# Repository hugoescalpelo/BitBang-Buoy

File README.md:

# BitBang-Buoy

A project from Iván Abreu's Studio to simulate wave movement through a pendant system

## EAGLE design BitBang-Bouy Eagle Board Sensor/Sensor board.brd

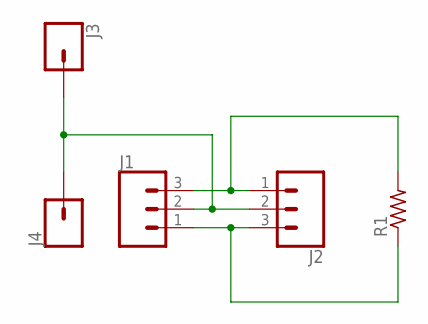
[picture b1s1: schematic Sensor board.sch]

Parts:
J1, J2: CONN_03LONGPADS; 1X03_LONGPADS
J3, J4: CONN_01SMTSO-256-ET-0.165DIA; SMTSO-256-ET-0.165DIA
R1: R-US_0204/7; 0204/7

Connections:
unnamed: J1.3, J2.1, R1.2
unnamed: J1.2, J2.2, J3.P$1, J4.P$1
unnamed: J1.1, J2.3, R1.1

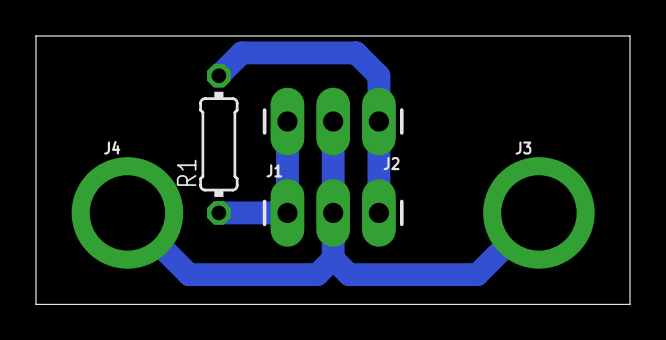
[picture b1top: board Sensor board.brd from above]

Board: 2 copper layers, 33.0 x 14.9 mm, 5 parts (0 on the bottom side), 3 nets.

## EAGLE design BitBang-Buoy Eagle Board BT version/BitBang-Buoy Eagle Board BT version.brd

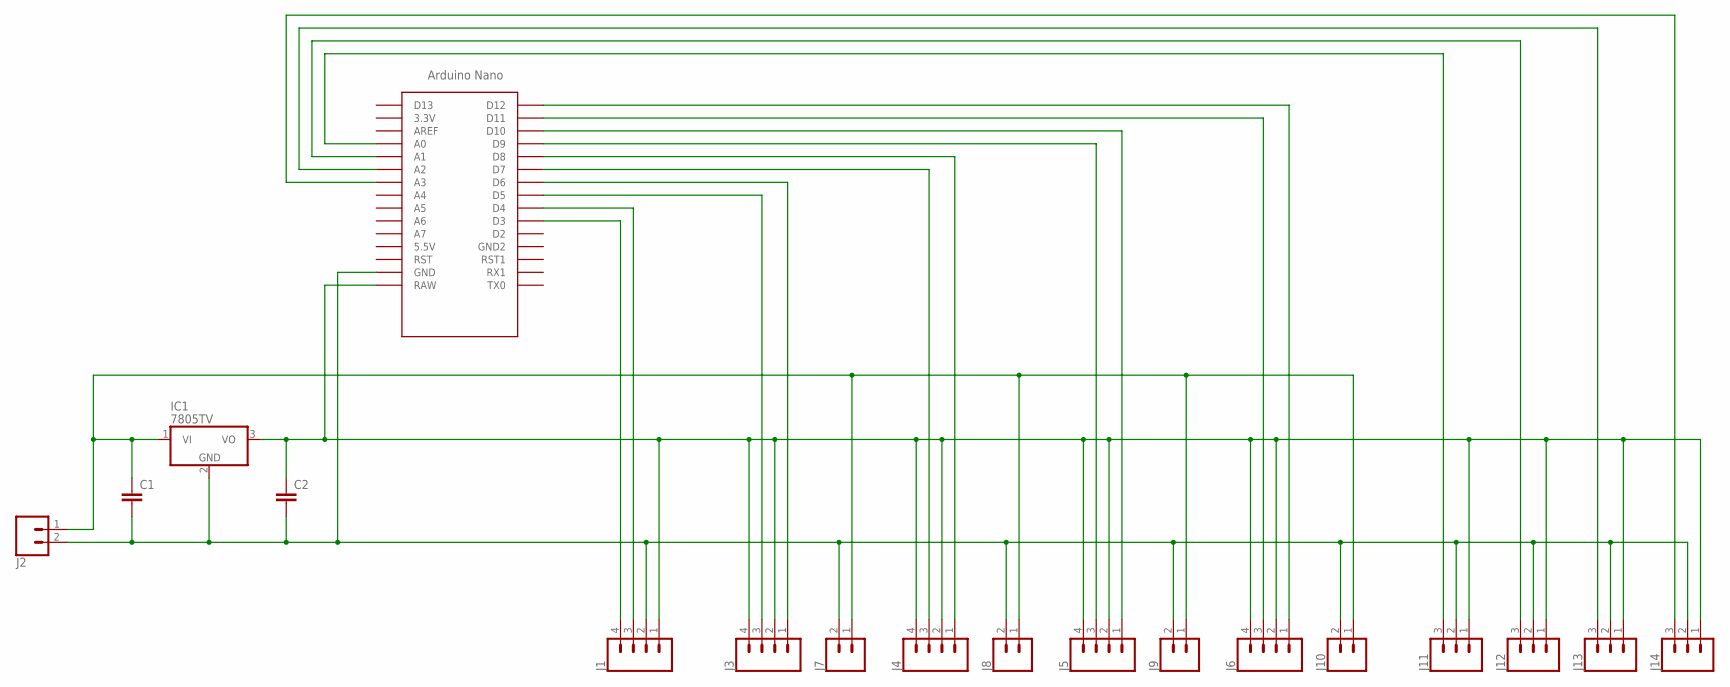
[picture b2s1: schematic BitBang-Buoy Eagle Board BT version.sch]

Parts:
C1, C2: C-EU050-024X044; C050-024X044
IC1: 7805TV; TO220V
J1: CONN_04LONGPADS; 1X04_LONGPADS
J2, J7, J8, J9, J10: CONN_023.5MM_LOCK; SCREWTERMINAL-3.5MM-2_LOCK
J3, J4, J5, J6: CONN_04SCREW_LOCK; SCREWTERMINAL-3.5MM-4_LOCK
J11, J12, J13, J14: CONN_03SCREW_LOCK; SCREWTERMINAL-3.5MM-3_LOCK.007S
U$1: NANO

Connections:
5V_R: C2.1, IC1.3 (VO), J1.1, J3.2, J3.4, J4.2, J4.4, J5.2, J5.4, J6.2, J6.4, J11.1, J12.1, J13.1, J14.1, U$1.RAW
12V: C1.1, IC1.1 (VI), J2.1, J7.1, J8.1, J9.1, J10.1
GND: C1.2, C2.2, IC1.2 (GND), J1.2, J2.2, J7.2, J8.2, J9.2, J10.2, J11.2, J12.2, J13.2, J14.2, U$1.GND
unnamed: J1.3, U$1.D4
unnamed: J1.4, U$1.D3
unnamed: J3.3, U$1.D5
unnamed: J3.1, U$1.D6
unnamed: J4.3, U$1.D7
unnamed: J4.1, U$1.D8
unnamed: J5.3, U$1.D9
unnamed: J5.1, U$1.D10
unnamed: J6.3, U$1.D11
unnamed: J6.1, U$1.D12
unnamed: J11.3, U$1.A0
unnamed: J12.3, U$1.A1
unnamed: J13.3, U$1.A2
unnamed: J14.3, U$1.A3

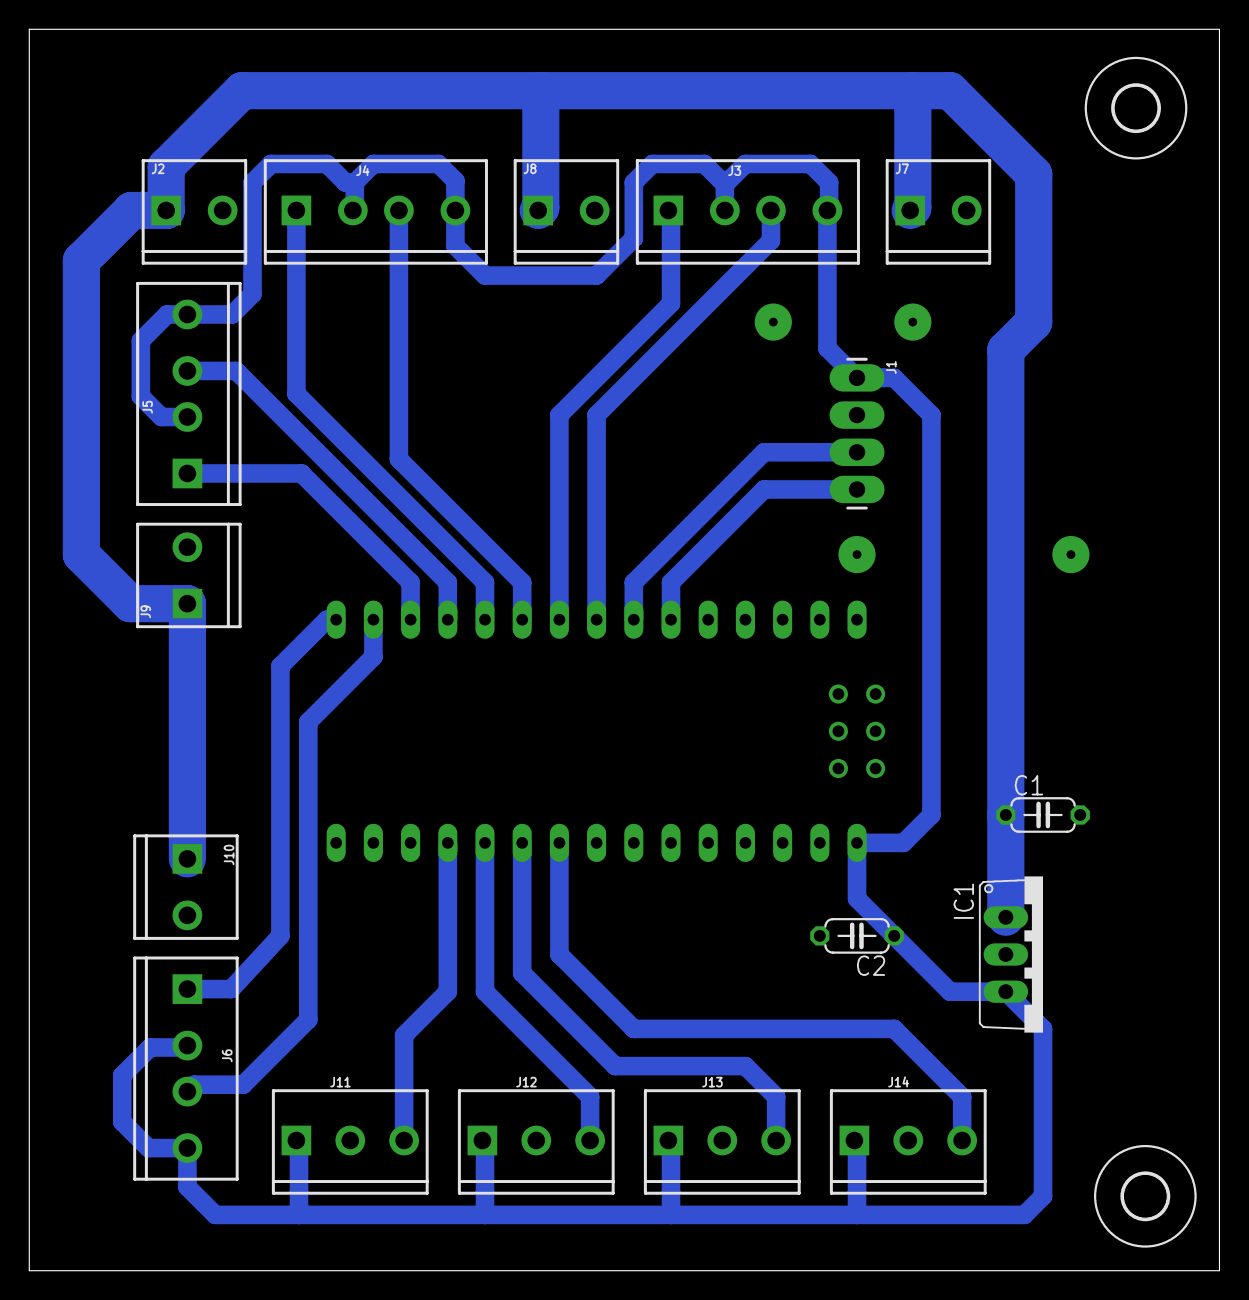
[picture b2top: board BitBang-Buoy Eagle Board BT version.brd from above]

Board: 2 copper layers, 81.3 x 84.8 mm, 20 parts (0 on the bottom side), 17 nets.

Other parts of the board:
H1, H2: MOUNT-HOLE3.0; 3,0

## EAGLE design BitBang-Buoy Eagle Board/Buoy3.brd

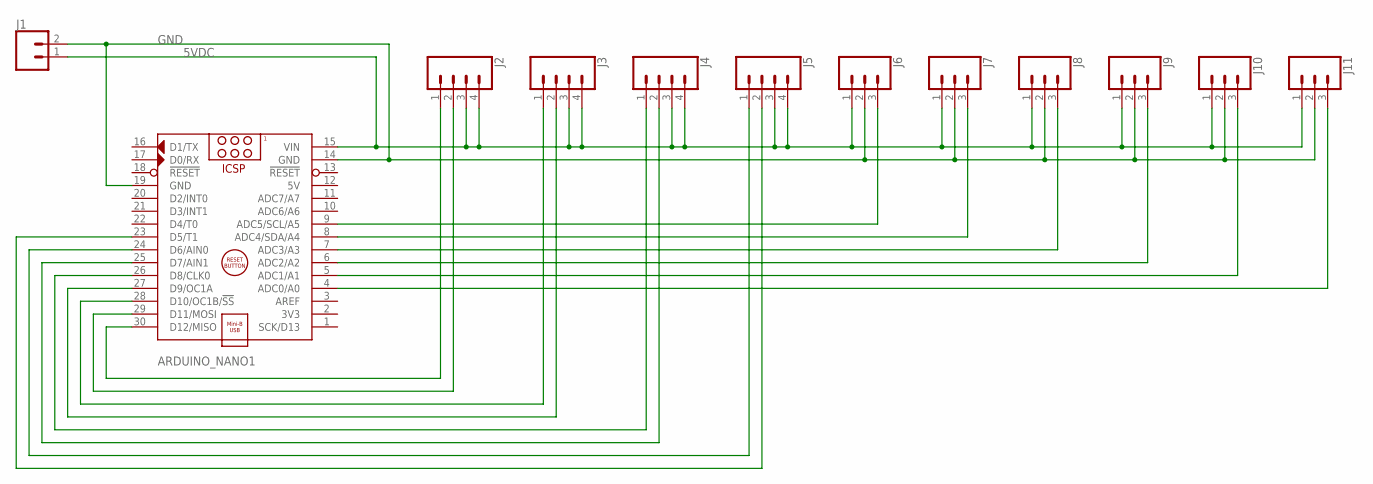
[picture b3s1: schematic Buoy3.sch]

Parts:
ARDUINO_NANO1: ARDUINO_NANO
J1: CONN_023.5MM_LOCK; SCREWTERMINAL-3.5MM-2_LOCK
J2, J3, J4, J5: CONN_04SCREW; SCREWTERMINAL-3.5MM-4
J6, J7, J8, J9, J10, J11: CONN_03SCREW_LOCK; SCREWTERMINAL-3.5MM-3_LOCK.007S

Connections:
5V: ARDUINO_NANO1.12 (5V)
5VDC: ARDUINO_NANO1.15 (VIN), J1.1, J2.3, J2.4, J3.3, J3.4, J4.3, J4.4, J5.3, J5.4, J6.1, J7.1, J8.1, J9.1, J10.1, J11.1
GND: ARDUINO_NANO1.14 (GND), ARDUINO_NANO1.19 (GND), J1.2, J6.2, J7.2, J8.2, J9.2, J10.2, J11.2
unnamed: ARDUINO_NANO1.30 (D12/MISO), J2.1
unnamed: ARDUINO_NANO1.29 (D11/MOSI), J2.2
unnamed: ARDUINO_NANO1.28 (D10/OC1B/!SS), J3.1
unnamed: ARDUINO_NANO1.27 (D9/OC1A), J3.2
unnamed: ARDUINO_NANO1.26 (D8/CLK0), J4.1
unnamed: ARDUINO_NANO1.25 (D7/AIN1), J4.2
unnamed: ARDUINO_NANO1.24 (D6/AIN0), J5.1
unnamed: ARDUINO_NANO1.23 (D5/T1), J5.2
unnamed: ARDUINO_NANO1.7 (ADC3/A3), J8.3
unnamed: ARDUINO_NANO1.4 (ADC0/A0), J11.3
unnamed: ARDUINO_NANO1.5 (ADC1/A1), J10.3
unnamed: ARDUINO_NANO1.6 (ADC2/A2), J9.3
unnamed: ARDUINO_NANO1.8 (ADC4/SDA/A4), J7.3
unnamed: ARDUINO_NANO1.9 (ADC5/SCL/A5), J6.3

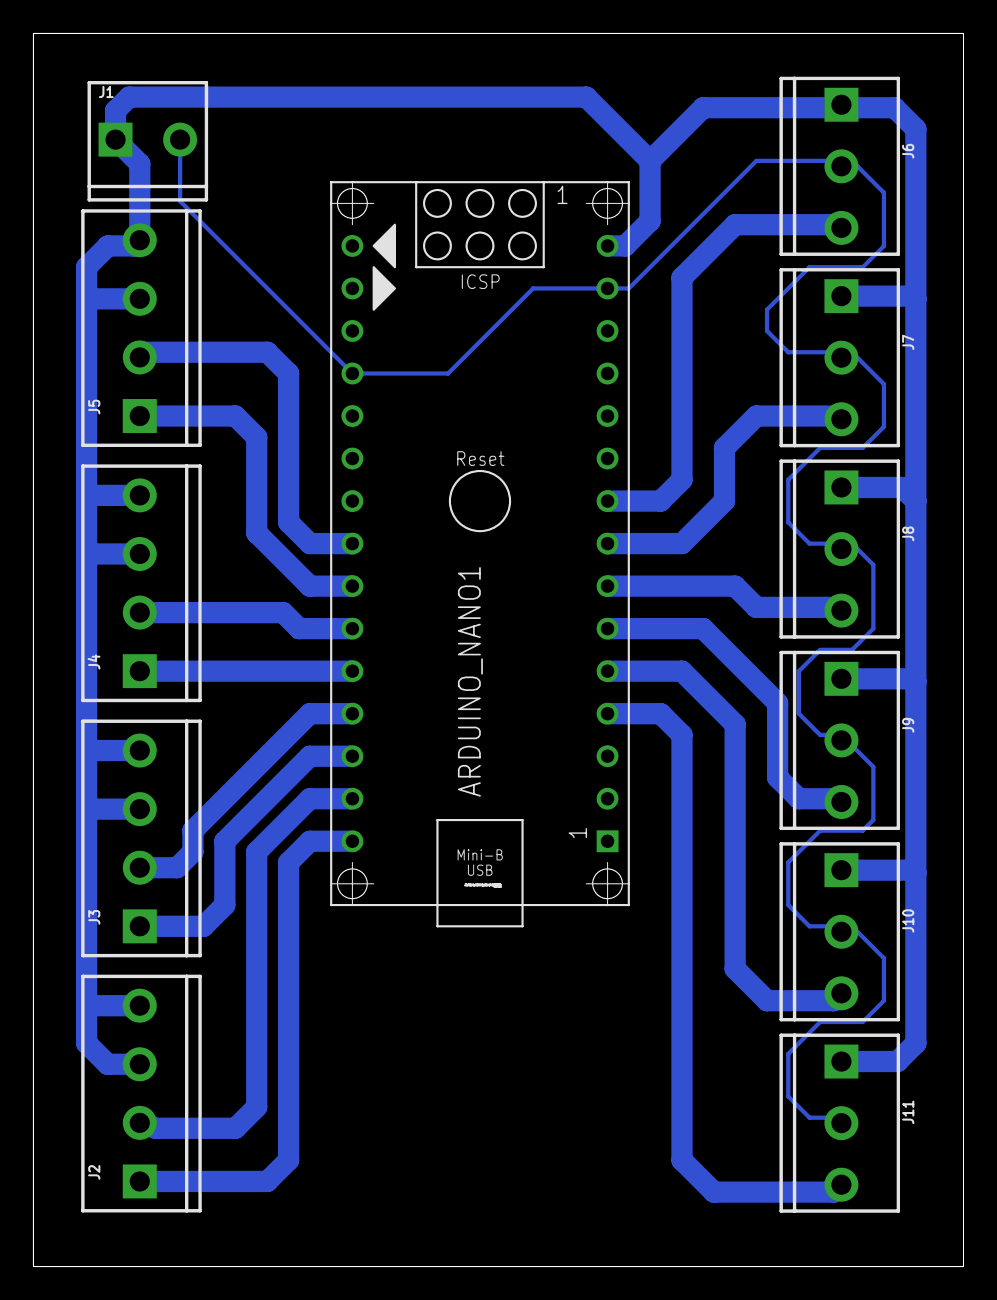
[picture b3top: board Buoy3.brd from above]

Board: 2 copper layers, 55.6 x 73.6 mm, 12 parts (0 on the bottom side), 16 nets.

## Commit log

2018-02-12 Version 1
2018-02-12 Ver 2
2018-02-12 Ver 3
2018-02-12 Ver 4
2018-02-12 Ver 5
2018-02-12 Ver 6
2018-02-12 Ver 7
2018-02-12 Ver 8
2018-02-12 Ver 9
2018-02-12 Ver 9
    Some details about the project added
2018-02-12 Version 9
    Added some files to pcb manufacture
2018-02-12 Log and readme description added
2018-02-15 CAM Files Added
2018-02-22 Golden combo generator added
2018-02-23 Manual-Forced Calibration sequence Added
    Code 1500
2018-02-27 Funny commentary
2018-03-15 BT board added
2018-03-15 Board finished
2018-03-15 Minor changes
2018-03-22 New pinout adapted
2018-05-18 Some changes
2018-06-25 Error correction
2018-07-06 Trascient detector added
    A trascient detector added in order to read mor accurately the hall sensor, it uses a registry ring and a window lecture
2018-07-06 Sensor Board resistance added
2018-08-02 Not connected values uploaded
    We change this because we are testing the artwork without a pc connected

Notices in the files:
parts and their libraries:
SparkFun-Connectors: Licensing: Creative Commons ShareAlike 4.0 International - https://creativecommons.org/licenses/by-sa/4.0
